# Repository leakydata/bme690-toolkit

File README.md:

# bme690-toolkit

Open tooling for Bosch's **BME690** and **BME688** gas sensors on Linux —
capture data, feed it to BME AI-Studio, and train models to recognise smells.

Bosch make excellent sensors and ship almost no usable software with them. The
shuttle boards arrive empty, AI-Studio is Windows-only and hard to even find,
and the file format that connects a capture to the training tool is
undocumented. This repository fills those gaps.

> Not affiliated with, endorsed by, or supported by Bosch Sensortec GmbH.

## What's here

| | |
|---|---|
| **[`bme690` CLI](python/)** | Reads all eight sensors on a BME690 8x shuttle over USB and writes AI-Studio-importable files |
| **[BME Studio](studio/)** | Browser app, an open alternative to BME AI-Studio: import, explore, label and train, with honest test scores and live predictions over USB. [Open it](https://leakydata.github.io/bme690-toolkit/studio/) |
| **[Python lab](python/LAB.md)** | `bme690.lab` for researchers with a GPU: pandas data loading, honest cross-validation, deep models across all sensors and over time, self-supervised pre-training, models back to BME Studio. Notebooks included |
| **[`.bmerawdata` format spec](docs/bmerawdata-format.md)** | The undocumented format AI-Studio imports, reverse-engineered and verified |
| **[Wiring guide](docs/wiring.md)** | Shuttle board and microSD to an ESP32-S3 DevKitC-1: diagram, pin tables with header positions, and the wiring check |
| **[Hardware notes](docs/hardware-notes.md)** | AB3.1 + shuttle pinout, flash layout, and the traps that cost days |
| **[AI-Studio on Linux](scripts/rebuild-aistudio-linux.sh)** | Turns Bosch's Windows release into a native Linux install |
| **[ESP32-S3 firmware](firmware/bme690-logger-idf/)** | Runs the shuttle from a cheap ESP32-S3 with no Application Board: records AI-Studio files to SD, WiFi dashboard, plain-English wiring diagnosis |

## Quick start

**No Application Board?** Wire the shuttle to an ESP32-S3 DevKitC and install
the firmware from your browser at
**[leakydata.github.io/bme690-toolkit](https://leakydata.github.io/bme690-toolkit/)**,
with nothing to install. That is the easiest way in, and what most people
should use. Details are in
[firmware/bme690-logger-idf](firmware/bme690-logger-idf/).

The rest of this section drives the shuttle on Bosch's Application Board 3.1
from a PC.

Hardware: a **BME690 8x shuttle board** on a **Bosch Application Board 3.1**,
running the stock `coines_bridge` firmware (how it ships), connected by USB.

```bash
git clone https://github.com/leakydata/bme690-toolkit
cd bme690-toolkit
python3 -m venv .venv && . .venv/bin/activate
pip install -e "python/[board]"

bme690 info      # board, firmware, all eight sensor IDs
bme690 read -n 5 # live readings from every sensor
```

You should see something like:

```
Board            : 0x9 (Application Board 3.1)
Shuttle          : 0x57
Firmware         : v1.8.6
Sensors detected : 8 -> [0, 1, 2, 3, 4, 5, 6, 7]
  sensor 0: chip 0x61  variant 2  uid 0xd737182e
  ...
```

Add yourself to the `dialout` group if the board is not reachable.

## Recording data for AI-Studio

```bash
# a labelled run: 5 min with the sample present, then 5 min of clean air
bme690 record -o coffee.bmerawdata --labels "coffee:300,air:300"
```

This writes `coffee.bmerawdata` and `coffee.bmelabelinfo`. In AI-Studio:
**Import Data → Specimen Raw Data**. The labelled segments arrive as named
specimens, ready to assign to classes and train on.

Defaults match Bosch's standard scanning setup: heater profile **HP-354**
(ten steps, 140 ms time base, 10.78 s per cycle), continuous duty cycle.

### Stabilise new sensors first

Factory-new sensors drift badly — gas resistance can move several-fold in
minutes. Bosch recommend at least 12 hours of stabilisation before any
training data is worth collecting:

```bash
bme690 burn-in --hours 12
```

Run it under `tmux`, somewhere with clean, still air.

## Commands

```
bme690 info                  board, firmware, sensor IDs
bme690 scan                  which sensor sockets answer
bme690 read -n 5 -i 2        forced-mode measurements
bme690 profiles              heater and duty cycle profiles AI-Studio knows
bme690 record -o F [...]     record a scan to .bmerawdata
bme690 burn-in --hours 12    stabilise the sensors
bme690 ingest -o F --port P  convert the ESP32-S3 logger's USB output to .bmerawdata
bme690 monitor [--port P]    live terminal view of the ESP32-S3 logger (curses)
```

### Two capture paths, one file format

| path | hardware | command |
|---|---|---|
| USB, host-driven | shuttle on an Application Board 3.1 | `bme690 record` |
| standalone firmware | shuttle on an ESP32-S3 | none: files are written to the SD card; or `bme690 ingest` over USB |

Both produce identical `.bmerawdata`, so captures from either import into the
same AI-Studio project.

```bash
# stream from the ESP32-S3 logger straight into a labelled capture
bme690 ingest --port /dev/ttyUSB0 -o coffee.bmerawdata --labels "coffee:300,air:300"

# or convert a log you captured earlier
cat /dev/ttyUSB0 > run.txt
bme690 ingest --from-file run.txt -o coffee.bmerawdata
```

`profiles` reads its catalogue from an AI-Studio installation, or from
`--config-dir` pointing at a directory holding `heater_profiles.json` and
`duty_cycle_profiles.json`.

## How it works

The Application Board 3.1 ships running Bosch's **COINES bridge firmware**,
which lets a host drive the shuttle board's SPI bus over USB. `bme690` talks
to it through the `coinespy` package, so **no reflashing is needed**.

- `device.py` — a Python port of Bosch's `bme69x.c` (float compensation path)
- `board.py` — the eight sensors and their SPI chip-selects
- `recorder.py` — parallel-mode scanning, where each sensor walks its ten-step
  heater profile autonomously and tags every result with the step index
- `rawdata.py` — the `.bmerawdata` / `.bmelabelinfo` writer

Two things that will bite you if you write your own: **coinespy takes volts,
not millivolts**, and **the SPI bus must be configured before the supply is
switched on**. Both are explained in [hardware notes](docs/hardware-notes.md);
`AppBoard31.open()` handles them.

## BME AI-Studio on Linux

AI-Studio is an Electron app, so its application code is portable JavaScript.
Only three native modules are Windows-specific — `better-sqlite3`, `sqlite3`
and `@tensorflow/tfjs-node`. Swap in Linux builds of the same versions, pair
with a Linux Electron 19.1.9 runtime, and it runs natively: project database,
TensorFlow training, BSEC export, all of it. No Wine.

```bash
scripts/rebuild-aistudio-linux.sh /path/to/bme_ai_studio_desktop_v3-1-0_win2
```

You supply Bosch's Windows release; the script contains no Bosch code.

## Which board is which

| board | interface | tooling |
|---|---|---|
| **BME690 8x shuttle** on an ESP32-S3 DevKitC | SD card, WiFi dashboard, USB | [firmware/bme690-logger-idf](firmware/bme690-logger-idf/) |
| **BME690 8x shuttle** on Application Board 3.1 | USB (COINES bridge) | `bme690`, this repo |
| **BME688 Development Kit** (8 sensors on ESP32) | SD card + BLE | AI-Studio board config + Bosch's mobile app |

The ESP32 dev kit runs its own autonomous firmware and is not driven by this
tool. Both produce `.bmerawdata`, so their data sits side by side in one
AI-Studio project — useful for cross-checking one sensor generation against
the other.

## Roadmap

The ESP32-S3 firmware does what the Application Board was meant to do:

- [x] Standalone scan, logging `.bmerawdata` to an SD card
- [x] Button and RGB LED: next sample label, start/stop
- [x] Retrieval by card reader or WiFi download
- [x] Heater profiles and duty cycles from AI-Studio `.bmeconfig` files
- [x] Wiring and sensor diagnosis in plain English
- [x] Built-in burn-in (Bosch HP-001)
- [x] Flash from the browser, so no toolchain is needed
- [ ] Battery operation
- [ ] BLE service and a phone app for field capture

`firmware/bme690-logger` is an earlier Zephyr build for a bare nRF52840. It is
no longer maintained and is kept for reference.

## Licensing

MIT, but it builds on Bosch software that is not. See
**[THIRD_PARTY.md](THIRD_PARTY.md)** — in short: the COINES SDK is fetched
rather than vendored, `coinespy` comes from PyPI, and BSEC and AI-Studio are
never distributed here.

```bash
scripts/setup-coines.sh   # needed only to build firmware
```

## Contributing

Issues and pull requests welcome — especially reports from other hardware
combinations. If you have a BME690 shuttle with a different EEPROM id, or an
AB3.1 with different firmware, please open an issue with `bme690 info` output.

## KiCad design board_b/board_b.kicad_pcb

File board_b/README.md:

# Board B: XIAO ESP32-S3 shuttle carrier

A 25.5 x 24.6 mm sandwich. A **Bosch Shuttle Board 3.0** plugs in on top
(made for the BME690 8x shuttle, and switchable to single-sensor shuttles).
A **Seeed XIAO ESP32-S3** or **XIAO ESP32-S3 Sense** plugs in underneath,
its USB-C at the P1 end.

**3.3 V only.** The XIAO's 3V3 pin powers the shuttle; it supplies up to
700 mA, and eight BME690 heaters need about 100 mA.

## Pin map

| XIAO | ESP32-S3 | shuttle | BME690 8x shuttle |
|---|---|---|---|
| D0 | GPIO1 | P1-4 (via JP2) | sensor U1 chip select |
| D1 | GPIO2 | P1-5 | U2 chip select |
| D2 | GPIO3 | P1-6 | U3 chip select |
| D3 | GPIO4 | P1-7 | U4 chip select |
| D4 | GPIO5 | P2-5 | U5 chip select |
| D5 | GPIO6 | P2-6 | U6 chip select |
| D6 | GPIO43 | P2-7 | U7 chip select |
| D7 | GPIO44 | P2-8 (via JP5) | U8 chip select |
| D8 | GPIO7 | P2-2 SCK/SCL | SPI clock |
| D9 | GPIO8 | P2-3 SDO | SPI data from the sensors (MISO) |
| D10 | GPIO9 | P2-4 SDI/SDA | SPI data to the sensors (MOSI) |
| 3V3 | | P1-2 VDDIO, and P1-1 VDD via JP1 | power |
| GND | | P1-3 | ground |
| 5V | | not connected | |

Two things about these pins:

- **D6 (GPIO43)** is the ESP32-S3's UART TX. The chip prints its boot
  messages there for a moment at power-up. That's harmless as a chip
  select, because nothing clocks the bus yet, but the firmware has to use
  the USB port for its console. The XIAO does this anyway.
- **D2 (GPIO3)** is a strapping pin, but only if the JTAG eFuse is burned;
  on a normal XIAO it's an ordinary GPIO.

### XIAO ESP32-S3 Sense

The Sense's microSD card uses **D8-D10 (the same SPI bus) plus GPIO21**
for its chip select. On this board the card and the sensors share one SPI
bus, each with its own chip select. On the Sense, GPIO21 is also the
orange user LED.

Seeed's design files suggest a catch, though. The Sense's camera/SD
expansion board is the XIAO's full width and covers the edge where header
pins are soldered. If so, a Sense with headers can't have its expansion
board fitted. Check yours: fit the expansion board and see whether the
pin holes along both long edges stay clear. Without the expansion board, a
Sense works here like a plain XIAO: live data over USB and WiFi, no card.

## Selector jumpers

**JP2 (D0) and JP5 (D7)** are 3-pad jumpers, made with **pads 1-2
joined** for the BME690 8x shuttle. The joined pair is the one with the
copper bridge.

| jumper | 1-2 (as made) | 2-3 |
|---|---|---|
| JP2 | D0 to shuttle GPIO0: U1 chip select (8x) | D0 to shuttle **CS**, for single-sensor shuttles |
| JP5 | D7 to shuttle GPIO7: U8 chip select (8x) | D7 to **PROM_RW**, the shuttle's ID chip |

**For a single-sensor shuttle**, cut the bridge on both and solder pads
2-3 together. With JP2 set this way, CS has a 10k pull-up, so the shuttle
starts in I2C mode; drive D0 low before the first transfer for SPI. Either
way its SCK/SDI/SDO are on D8/D10/D9, and its INT1/INT2 (P1-6, P1-7) are
on D2/D3.

### Other jumpers

All of these are closed as made:

| jumper | label | open it to |
|---|---|---|
| JP1 | IDD | measure sensor current: put a meter across J3 |
| JP3 | SDA | remove the 4.7k SDA pull-up |
| JP4 | SCL | remove the 4.7k SCL pull-up |

VDDIO is wired straight to the XIAO's 3V3, because it must match the XIAO's
logic level. So unlike Board A there is no TIE jumper.

PROM_RW has a 1k pull-up (the DS28E05 datasheet requires 300-1500 ohm). Its
1-Wire timing is overdrive only; see `board_a/README.md`.

## Assembly

JLCPCB fits the eight 0603 parts on top. You solder the rest:

1. **XIAO sockets first,** on the **bottom** (the side with the XIAO
   outline and "USB"). Plug both 1x7 sockets onto the XIAO's headers and
   set the XIAO in place. That holds them straight and 15.24 mm apart.
   Tack one pin of each, check they're square, then solder the rest from
   the top side.
2. **Trim their pins flush** on the top side. The shuttle sits above them.
3. **Shuttle sockets** on the **top**. Hold them in place with the shuttle,
   as described in board A's README.
4. **J3** (optional), on top.
5. Check with a meter: 3V3 to GND is **not** a short.

Solder the XIAO's own pin headers with the long pins coming out of its
underside, the side without the USB connector, as usual. The XIAO then
plugs in with its USB-C at the P1 end, and its buttons and antenna jack
facing away from the board.

## Firmware

The logger firmware has a build for this board (from version 2.4), with the
same dashboard, AI-Studio files and features as the DevKitC version:

| how | what to do |
|---|---|
| browser | at [leakydata.github.io/bme690-toolkit](https://leakydata.github.io/bme690-toolkit/), click **Install for XIAO ESP32-S3 (Board B)**. If the port doesn't appear, hold the XIAO's B button while plugging it in |
| WiFi update | `bme690-logger-xiao-app.bin`, from the same page |
| from source | `idf.py -B build-xiao -DBME690_BOARD=xiao build` in `firmware/bme690-logger-idf` |

What's different on the XIAO:

- **A plain XIAO ESP32-S3 works too**, live only: the dashboard's live
  graphs, **Record here** (recording into your browser), and USB streaming
  to BME Studio or the `bme690` tool. With no card, the dashboard shows a
  note (not a warning) and the LED blinks normally. Card recording needs
  the Sense with its camera/SD board fitted.
- The serial console is the XIAO's USB-C.
- The orange LED blinks the status: long = recording, short = not
  recording, double = warning or problem. It stays off while a Sense card
  is mounted, because on the Sense the LED pin is the card's chip select.
- The Sense's card shares the sensor bus. The firmware switches every
  sensor to SPI mode before the card is touched, and locks the bus for
  each transfer, so the two never talk over each other.

**Not yet tested on hardware.** Both builds compile cleanly. The first
power-up should be checked on the dashboard's Health tab.

## Ordering at JLCPCB

Everything is in `fab/`, in the same format as Board A:

| file | upload as |
|---|---|
| `board_b-gerbers.zip` | the PCB |
| `board_b-bom-jlcpcb.csv` | PCB Assembly: BOM |
| `board_b-cpl-jlcpcb.csv` | PCB Assembly: CPL |

The options, coupon notes and pre-order checklist are the same as in
`board_a/README.md`, with these differences:

| check | Board B |
|---|---|
| board size | 25.5 x 24.6 mm |
| holes | 42 (10 vias, 16 shuttle socket holes, 16 header holes) |
| assembly | Economic, top side |
| SMD parts | the same eight Basic parts as Board A |

### Parts JLCPCB fits

| parts | value | LCSC |
|---|---|---|
| R1, R2 | 4.7k 0603 | C23162 |
| R3 | 1k 0603 | C21190 |
| R4 | 10k 0603 | C25804 |
| C1, C3 | 100 nF 0603 | C14663 |
| C2, C4 | 10 uF 0603 | C19702 |

All are Basic; stock was checked 2026-10-05.

### Parts you buy

Per board:

| part | qty | about |
|---|---|---|
| Sullins LPPB071NFFN-RC, 7-pin 1.27 mm socket | 1 | $1.00 |
| Sullins LPPB091NFFN-RC, 9-pin 1.27 mm socket | 1 | $1.20 |
| Sullins PPTC071LFBN-RC, 1x7 female 2.54 mm, 8.5 mm tall | 2 | $0.70 each |
| 1x2 male header, 2.54 mm (optional, for IDD) | 1 | $0.05 |
| Seeed XIAO ESP32-S3 (or the Sense) | 1 | see seeedstudio.com |

## Cost estimate, 5 boards

The same as Board A, since it uses the same eight parts on a board under
100 x 100 mm:

| order | before shipping | with shipping and duty |
|---|---|---|
| bare PCBs | about $3-4 | about $7-10 by the cheapest shipping |
| PCB + Economic assembly | about $13-15 | about $17-22 |

**Ordering A and B together:** two designs are two PCB line items. The
assembly setup and stencil fees ($8.18 + $1.53) are charged per design,
but you pay shipping once.

## Design rules

The same JLCPCB rules as Board A. Results: ERC 0, DRC 0 (warnings
included), schematic parity 0.

The XIAO footprint's courtyard covers its two sockets only. The module
itself rides 8.5 mm up on them, well above the shuttle socket's 3 mm pin
tails that pass beneath it. DRC therefore doesn't flag those tails.

## Editing

Open `board_b.kicad_pro` in KiCad 10. `build.py` and `pcb.py` generated
the first version. Edit in KiCad from here on; re-running the scripts
overwrites your changes.

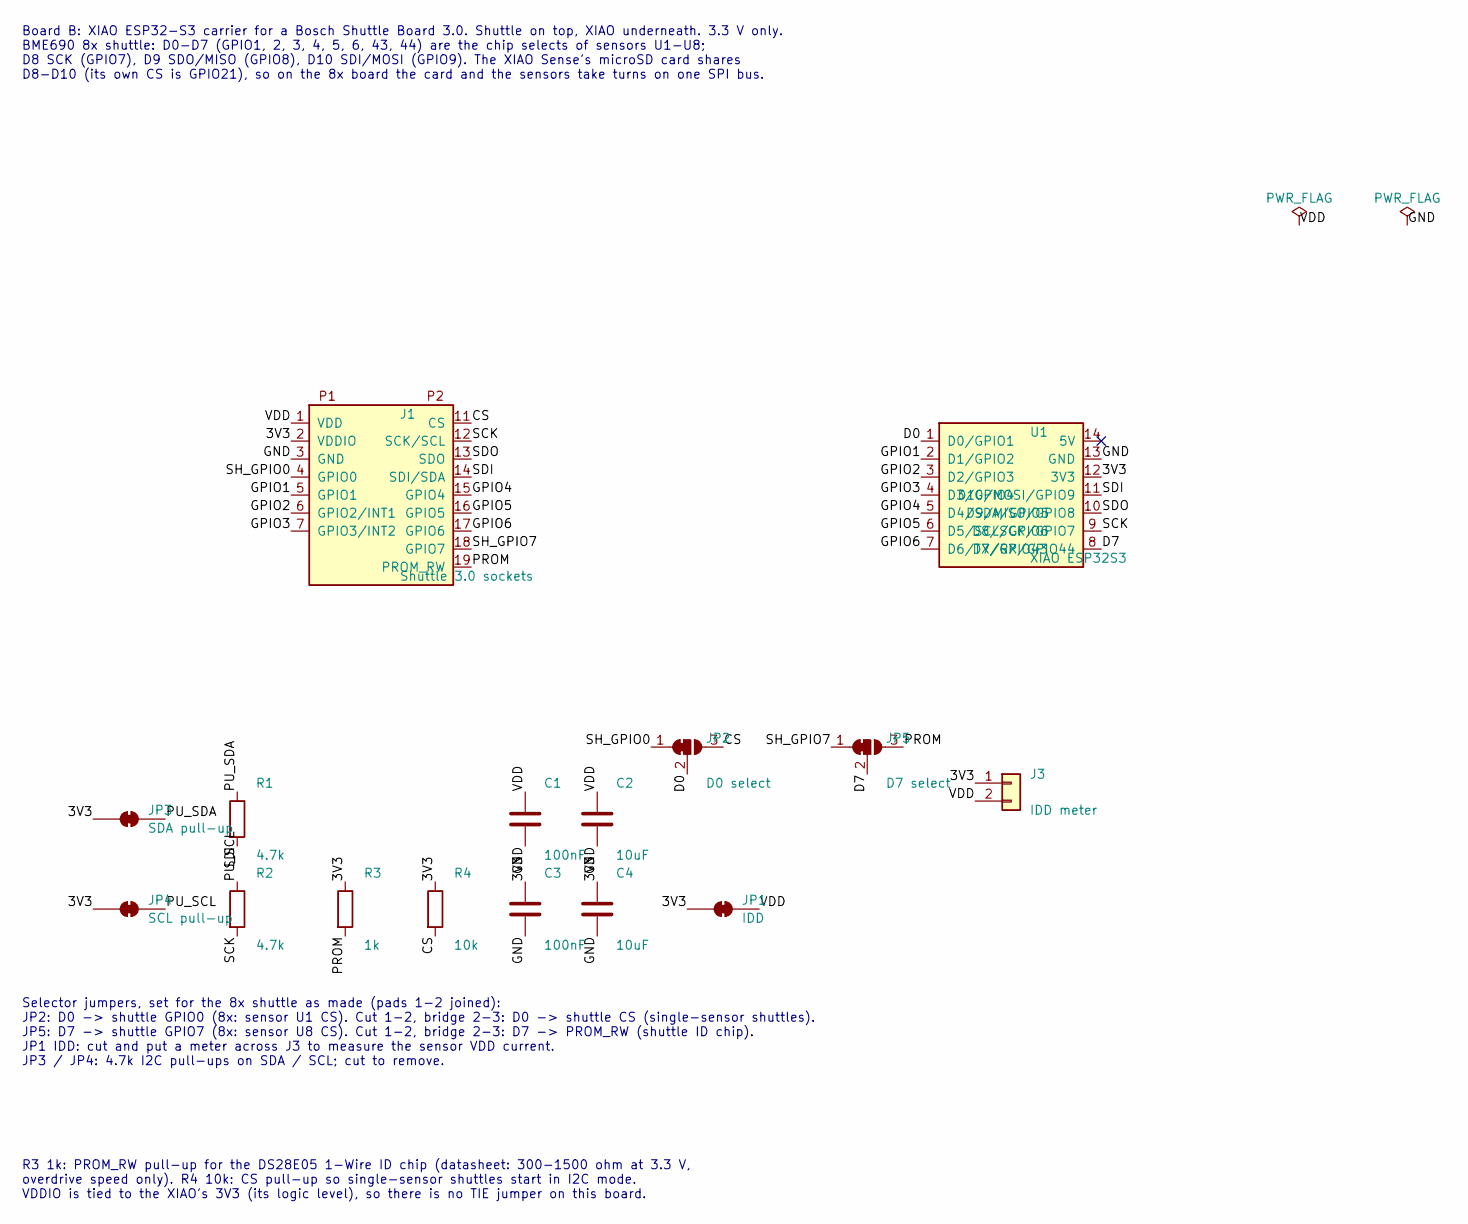
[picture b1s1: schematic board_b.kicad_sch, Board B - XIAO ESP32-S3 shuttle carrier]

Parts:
C1, C3: 100nF; C_0603_1608Metric; LCSC C14663
C2, C4: 10uF; C_0603_1608Metric; LCSC C19702
J1: Shuttle 3.0 sockets; Bosch_Shuttle_3.0_Sockets; MPN Sullins LPPB071NFFN-RC + LPPB091NFFN-RC
J3: IDD meter; PinHeader_1x02_P2.54mm_Vertical; MPN 1x2 male header 2.54 mm
JP1: IDD; SolderJumper-2_P1.3mm_Bridged_RoundedPad1.0x1.5mm
JP2: D0 select; SolderJumper-3_P1.3mm_Bridged12_RoundedPad1.0x1.5mm
JP3: SDA pull-up; SolderJumper-2_P1.3mm_Bridged_RoundedPad1.0x1.5mm
JP4: SCL pull-up; SolderJumper-2_P1.3mm_Bridged_RoundedPad1.0x1.5mm
JP5: D7 select; SolderJumper-3_P1.3mm_Bridged12_RoundedPad1.0x1.5mm
R1, R2: 4.7k; R_0603_1608Metric; LCSC C23162
R3: 1k; R_0603_1608Metric; LCSC C21190
R4: 10k; R_0603_1608Metric; LCSC C25804
U1: XIAO ESP32S3; XIAO_ESP32S3_THT; MPN 2x Sullins PPTC071LFBN-RC (1x7 female 2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

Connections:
/3V3: C3.1, C4.1, J1.2 (VDDIO), J3.1, JP1.1 (A), JP3.1 (A), JP4.1 (A), R3.1, R4.1, U1.12 (3V3)
/CS: J1.11 (CS), JP2.3 (B), R4.2
/D0: JP2.2 (C), U1.1 (D0/GPIO1)
/D7: JP5.2 (C), U1.8 (D7/RX/GPIO44)
/GND: C1.2, C2.2, C3.2, C4.2, J1.3 (GND), U1.13 (GND)
/GPIO1: J1.5 (GPIO1), U1.2 (D1/GPIO2)
/GPIO2: J1.6 (GPIO2/INT1), U1.3 (D2/GPIO3)
/GPIO3: J1.7 (GPIO3/INT2), U1.4 (D3/GPIO4)
/GPIO4: J1.15 (GPIO4), U1.5 (D4/SDA/GPIO5)
/GPIO5: J1.16 (GPIO5), U1.6 (D5/SCL/GPIO6)
/GPIO6: J1.17 (GPIO6), U1.7 (D6/TX/GPIO43)
/PROM: J1.19 (PROM_RW), JP5.3 (B), R3.2
/PU_SCL: JP4.2 (B), R2.1
/PU_SDA: JP3.2 (B), R1.1
/SCK: J1.12 (SCK/SCL), R2.2, U1.9 (D8/SCK/GPIO7)
/SDI: J1.14 (SDI/SDA), R1.2, U1.11 (D10/MOSI/GPIO9)
/SDO: J1.13 (SDO), U1.10 (D9/MISO/GPIO8)
/SH_GPIO0: J1.4 (GPIO0), JP2.1 (A)
/SH_GPIO7: J1.18 (GPIO7), JP5.1 (A)
/VDD: C1.1, C2.1, J1.1 (VDD), J3.2, JP1.2 (B)

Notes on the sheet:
Board B: XIAO ESP32-S3 carrier for a Bosch Shuttle Board 3.0. Shuttle on top, XIAO underneath. 3.3 V only. BME690 8x shuttle: D0-D7 (GPIO1, 2, 3, 4, 5, 6, 43, 44) are the chip selects of sensors U1-U8; D8 SCK (GPIO7), D9 SDO/MISO (GPIO8), D10 SDI/MOSI (GPIO9). The XIAO Sense's microSD card shares D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
Selector jumpers, set for the 8x shuttle as made (pads 1-2 joined): JP2: D0 -> shuttle GPIO0 (8x: sensor U1 CS). Cut 1-2, bridge 2-3: D0 -> shuttle CS (single-sensor shuttles). JP5: D7 -> shuttle GPIO7 (8x: sensor U8 CS). Cut 1-2, bridge 2-3: D7 -> PROM_RW (shuttle ID chip). JP1 IDD: cut and put a 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
R3 1k: PROM_RW pull-up for the DS28E05 1-Wire ID chip (datasheet: 300-1500 ohm at 3.3 V, overdrive speed only). R4 10k: CS pull-up so single-sensor shuttles start in I2C mode. VDDIO is tied to the XIAO's 3V3 (its logic level), so there is no TIE jumper on this board.

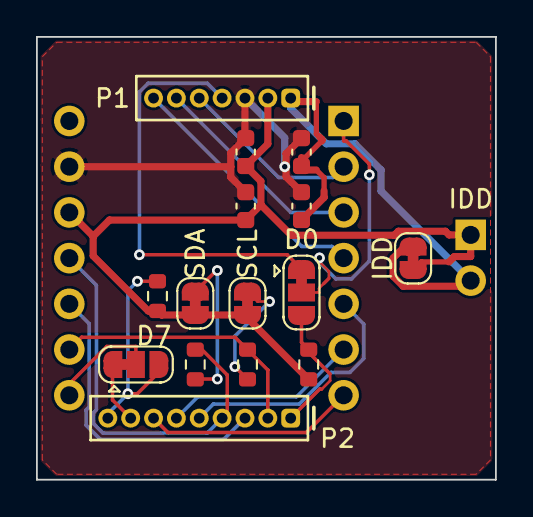
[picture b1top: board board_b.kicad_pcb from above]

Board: 2 copper layers, 25.5 x 24.6 mm, 16 parts (1 on the bottom side), 20 nets.

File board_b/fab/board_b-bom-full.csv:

Designator,Value,Footprint,LCSC,MPN,Fitted by
C1,100nF,C_0603_1608Metric,C14663,,JLCPCB
C2,10uF,C_0603_1608Metric,C19702,,JLCPCB
C3,100nF,C_0603_1608Metric,C14663,,JLCPCB
C4,10uF,C_0603_1608Metric,C19702,,JLCPCB
J1,Shuttle 3.0 sockets,Bosch_Shuttle_3.0_Sockets,,Sullins LPPB071NFFN-RC + LPPB091NFFN-RC,you (hand solder)
J3,IDD meter,PinHeader_1x02_P2.54mm_Vertical,,1x2 male header 2.54 mm,you (hand solder)
R1,4.7k,R_0603_1608Metric,C23162,,JLCPCB
R2,4.7k,R_0603_1608Metric,C23162,,JLCPCB
R3,1k,R_0603_1608Metric,C21190,,JLCPCB
R4,10k,R_0603_1608Metric,C25804,,JLCPCB
U1,XIAO ESP32S3,XIAO_ESP32S3_THT,,"2x Sullins PPTC071LFBN-RC (1x7 female 2.54 mm, 8.5 mm) for a Seeed XIAO ESP32S3 / Sense",you (hand solder)

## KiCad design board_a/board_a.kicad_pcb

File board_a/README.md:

# Board A: Shuttle 3.0 breakout

A 29.3 x 26.2 mm board that takes **any Bosch Sensortec Shuttle Board 3.0**,
including the BME690 8x shuttle, and brings all 16 of its pins out to a
labelled 2.54 mm header for Dupont wires, a breadboard ribbon or a
microcontroller.

## What's on it

| part | job |
|---|---|
| J1 | shuttle sockets: P1 (7 pins) and P2 (9 pins), 1.27 mm. A 7-pin and a 9-pin socket, so the shuttle only fits one way |
| J2 | 2x8 2.54 mm header with every shuttle pin |
| J3 | 2 pins for measuring the sensor's VDD current (IDD) |
| R1, R2 | 4.7k I2C pull-ups on SDA and SCL, each behind a cut jumper |
| R3 | 1k pull-up on PROM_RW, the shuttle's ID chip |
| R4 | 10k pull-up on CS, so single-sensor shuttles start in I2C mode |
| C1-C4 | 100 nF + 10 uF on VDD, and the same on VDDIO |

**3.3 V only. Never connect 5 V.**

## Header pin map (J2)

The column next to the shuttle carries its GPIO0-7, and the outer column
carries power and the bus. Both sides of the board are labelled, and a dot
marks pin 1.

| row | inner pin | inner label | signal | outer pin | outer label | signal |
|---|---|---|---|---|---|---|
| 1 | 1 | 0 | GPIO0 (P1-4) | 2 | VIO | VDDIO (P1-2) |
| 2 | 3 | 1 | GPIO1 (P1-5) | 4 | VDD | VDD supply in |
| 3 | 5 | 2 | GPIO2/INT1 (P1-6) | 6 | GND | GND (P1-3) |
| 4 | 7 | 3 | GPIO3/INT2 (P1-7) | 8 | SCK | SCK/SCL (P2-2) |
| 5 | 9 | 4 | GPIO4 (P2-5) | 10 | SDO | SDO (P2-3) |
| 6 | 11 | 5 | GPIO5 (P2-6) | 12 | SDI | SDI/SDA (P2-4) |
| 7 | 13 | 6 | GPIO6 (P2-7) | 14 | CS | CS (P2-1) |
| 8 | 15 | 7 | GPIO7 (P2-8) | 16 | ID | PROM_RW (P2-9) |

On the **BME690 8x shuttle**, GPIO0-7 are the chip selects of sensors
U1-U8, and CS (P2-1) isn't connected to anything. The 8x shuttle only works
over SPI: in I2C mode all eight sensors would answer at the same address.

## Solder jumpers

All four are **closed as made**. To open one, cut the thin trace between
its pads with a sharp knife. To close it again, bridge the pads with solder.

| jumper | label | open it to |
|---|---|---|
| JP1 | IDD (bottom left of J3) | measure sensor current: put a meter across J3 |
| JP2 | TIE | power VDDIO separately from VDD (feed VIO yourself) |
| JP3 | SDA | remove the 4.7k SDA pull-up |
| JP4 | SCL | remove the 4.7k SCL pull-up |

With TIE closed, one 3.3 V wire to **VIO** or **VDD** powers everything.

## Which side for the header?

The header is hand-soldered, so you choose:

- **Pins down, on the back:** best for sniffing jars. The sensors face the
  sample and the wires leave from the other side, so the plastic and wire
  insulation stay out of the air being measured.
- **Pins up, on the front:** easiest on a bench.
- **Right-angle header:** the wires leave sideways and the board lies flat.
  Its body covers the labels on that side, but the other side is labelled
  too.

**To a breadboard:** use a 16-way ribbon cable with a 2x8 IDC socket on
one end and a 16-pin DIP IDC plug on the other. Put the red stripe at the
pin-1 dot. The plug sits across the breadboard's centre gap. Its pins
alternate between the two DIP rows, so check the plug's datasheet for which
conductor lands where. A flat ribbon also passes a jar lid's seal far
better than loose jumpers.

## Assembly

JLCPCB fits the eight 0603 parts. You solder the through-hole parts.

1. Check the board under a light: all eight SMD parts present, no bridges.
2. **Sockets first.** Plug both sockets onto the shuttle and push the
   shuttle into the board. The shuttle holds the sockets straight and at
   the right spacing. Solder one end pin of each row, check they sit flat,
   then solder the rest. Remove the shuttle before it gets hot for long.
3. **2x8 header** on the side you chose. Solder one pin, check it's square,
   then the rest.
4. **J3** (optional), the same way.
5. Check with a meter: 3V3 to GND must **not** be a short. VIO to VDD
   reads about 0 ohm (TIE closed).

## Smoke test (ESP32-S3)

`smoke_test/smoke_test.ino` (Arduino IDE or arduino-cli, ESP32 core 3.x,
board "ESP32S3 Dev Module"). The wiring matches the logger firmware's pin
map, so a board wired for the logger runs the test unchanged.

| Board A | ESP32-S3 |
|---|---|
| VIO | 3V3 |
| GND | GND |
| SCK | GPIO12 |
| SDI | GPIO11 |
| SDO | GPIO13 |
| 0-7 | GPIO1, 2, 4, 5, 6, 7, 15, 16 |

- `MODE_SPI 1` (the default), for the 8x shuttle: reads the chip ID
  register of all eight sensors and expects **0x61** from each. A sensor
  that answers wrong names its chip-select wire.
- `MODE_SPI 0`, for a single-sensor shuttle: scans I2C and reads register
  0xD0 at **0x76**. It drives SDO low to set that address, because SDO
  must not float. Expect 0x61. Leave CS open; the 10k pull-up selects I2C.

For the full logger, see `firmware/bme690-logger-idf`.

**PROM_RW (shuttle ID):** the DS28E05 talks at 1-Wire **overdrive speed
only** (up to 76.9 kbps). The datasheet's overdrive timings are:

| timing | value |
|---|---|
| reset low | 48-80 us |
| presence sample | 8-10 us |
| write-0 low | 8-16 us |
| write-1 / read low | 1-2 us |
| sample by | 2 us |
| slot | 13 us minimum |
| EEPROM write | 16 ms per write |

Common ESP32 1-Wire libraries run at standard speed and won't see it. A
reader needs these timings, using the RMT peripheral or interrupt-free bit
timing. It isn't in the smoke test yet.

## Ordering at JLCPCB

All files are in `fab/`:

| file | upload as |
|---|---|
| `board_a-gerbers.zip` | the PCB (Gerbers + Excellon drill) |
| `board_a-bom-jlcpcb.csv` | PCB Assembly: BOM |
| `board_a-cpl-jlcpcb.csv` | PCB Assembly: CPL / pick-and-place |
| `board_a-bom-full.csv` | your shopping list, including the hand-soldered parts |
| `board_a-schematic.pdf`, `board_a-layout.pdf` | for checking |

**Board options:**

| option | setting |
|---|---|
| layers | 2 |
| thickness | 1.6 mm |
| material | FR-4 |
| solder mask | green |
| surface finish | **LeadFree HASL** |
| Mark on PCB | **Remove Mark** (free, and the default) |
| quantity | 5 |

**Assembly options:**

| option | setting |
|---|---|
| type | Economic |
| side | Top |
| boards to assemble | 5 (or 2, the minimum) |

### Parts JLCPCB fits

All are LCSC **Basic** parts, so there is no extended-part fee. Stock was
checked 2026-10-05.

| parts | value | LCSC | stock |
|---|---|---|---|
| R1, R2 | 4.7k 1% 0603 | C23162 | 22.2 M |
| R3 | 1k 1% 0603 | C21190 | 21.3 M |
| R4 | 10k 1% 0603 | C25804 | 29.6 M |
| C1, C3 | 100 nF X7R 50 V 0603 | C14663 | 57.2 M |
| C2, C4 | 10 uF X5R 10 V 0603 | C19702 | 10.3 M |

### Parts you buy and solder

Per board:

| part | qty | about |
|---|---|---|
| Sullins LPPB071NFFN-RC, 7-pin 1.27 mm socket | 1 | $1.00 |
| Sullins LPPB091NFFN-RC, 9-pin 1.27 mm socket | 1 | $1.20 |
| 2x8 male header, 2.54 mm (straight or right angle) | 1 | $0.30 |
| 1x2 male header, 2.54 mm (optional, for IDD) | 1 | $0.05 |

## Cost estimate, 5 boards

These are estimates from JLCPCB's published prices (October 2026). The quote
page gives the real figure.

| | bare PCB | PCB + assembly |
|---|---|---|
| 5 PCBs, 2-layer, under 100 x 100 mm | $2 | $2 |
| lead-free HASL surcharge | about $1-1.50 | about $1-1.50 |
| assembly setup (Economic) | - | $8.18 |
| stencil | - | $1.53 |
| solder joints, 80 x $0.0016 | - | $0.13 |
| parts: 5 Basic lines, LCSC minimum quantities | - | about $0.50-1 |
| extended-part fees | - | $0 (none) |
| **subtotal before shipping** | **about $3-4** | **about $13-15** |
| US shipping, Global Standard Direct (slowest, cheapest) | about $1.50-4 | about $2-5 |
| US shipping, DHL / UPS / FedEx express | about $15-25 | about $15-25 |
| US import duty (DDP, pre-collected) | a few dollars | a few dollars |

Plus about $13 for the hand-soldered parts for 5 boards, with distributor
shipping on top.

**Duties.** JLCPCB ships to US individuals **DDP (Delivered Duty Paid)**:
the import duty is calculated and charged at checkout, so nothing is due on
delivery. It is mandatory for individual customers. Business accounts may
choose CPT and pay duty themselves. JLCPCB revised its US rates on
2026-03-17, after the February 2026 tariff change. The exact amount appears
on the checkout page.

**Coupons.**
- **When it applies:** the coupon is chosen on the **checkout / payment
  page**, after you enter the shipping address. Available coupons are
  listed there, and a code (such as a YouTube sponsor code) goes in the
  coupon box on the right of the order summary.
- **One per order:** only one coupon can be used per order, and coupons
  can't be combined. Pick the larger of your sponsor code and the
  new-customer coupon.
- **New-customer coupons:** $6 off PCB orders over $2, or $10 off SMT
  assembly orders over $2, with **shipping not counted** toward the
  minimum. A separate $10 shipping coupon needs $15 of shipping.

### Pre-order checklist

1. Upload `board_a-gerbers.zip`. The viewer should show 29.3 x 26.2 mm,
   2 layers and 39 holes, with the labels readable on both sides.
2. Set LeadFree HASL, green, 1.6 mm, and leave "Mark on PCB" at
   **Remove Mark**.
3. Turn on PCB Assembly: Economic, Top side, then upload the BOM and CPL.
4. On the parts page, check that all 8 parts matched (5 lines, all
   "Basic") and nothing is marked "shortage".
5. On the placement preview, check each part sits on its pads. R and C
   rotation doesn't matter (they aren't polarised), but each must sit
   squarely on both pads.
6. Choose shipping and check the DDP duty line.
7. Apply your coupon on the checkout page and check the total before
   paying.
8. Order the sockets and headers from a distributor (Digi-Key, Mouser,
   LCSC) at the same time.

## Design rules used

JLCPCB 2-layer capabilities (jlcpcb.com/capabilities, checked 2026-10-03),
with these values used:

| rule | used | JLCPCB minimum |
|---|---|---|
| clearance | 0.15 mm | 0.10 mm |
| minimum track | 0.15 mm (0.2 signal, 0.4 power) | 0.10 mm |
| vias | 0.6 mm pad, 0.3 mm hole | 0.25 / 0.15 mm |
| PTH annular ring | at least 0.225 mm (sockets) | 0.18 mm (0.25 recommended) |
| copper to board edge | 0.3 mm | 0.2 mm |
| hole to hole | 0.5 mm | 0.45 mm |
| silkscreen text | 1.0 mm high, 0.15 mm line | 1.0 / 0.15 mm |

ERC: 0 errors, 0 warnings. DRC, including warnings and schematic parity: 0.

## Editing

Open `board_a.kicad_pro` in KiCad 10. `build.py` and `pcb.py` generated
the first version: one parts list feeds both the schematic and the board,
with Freerouting for the tracks. Once you edit in KiCad, keep editing there.
Re-running the scripts overwrites your changes. The shared symbols and
footprints are in `../shuttle_lib`.

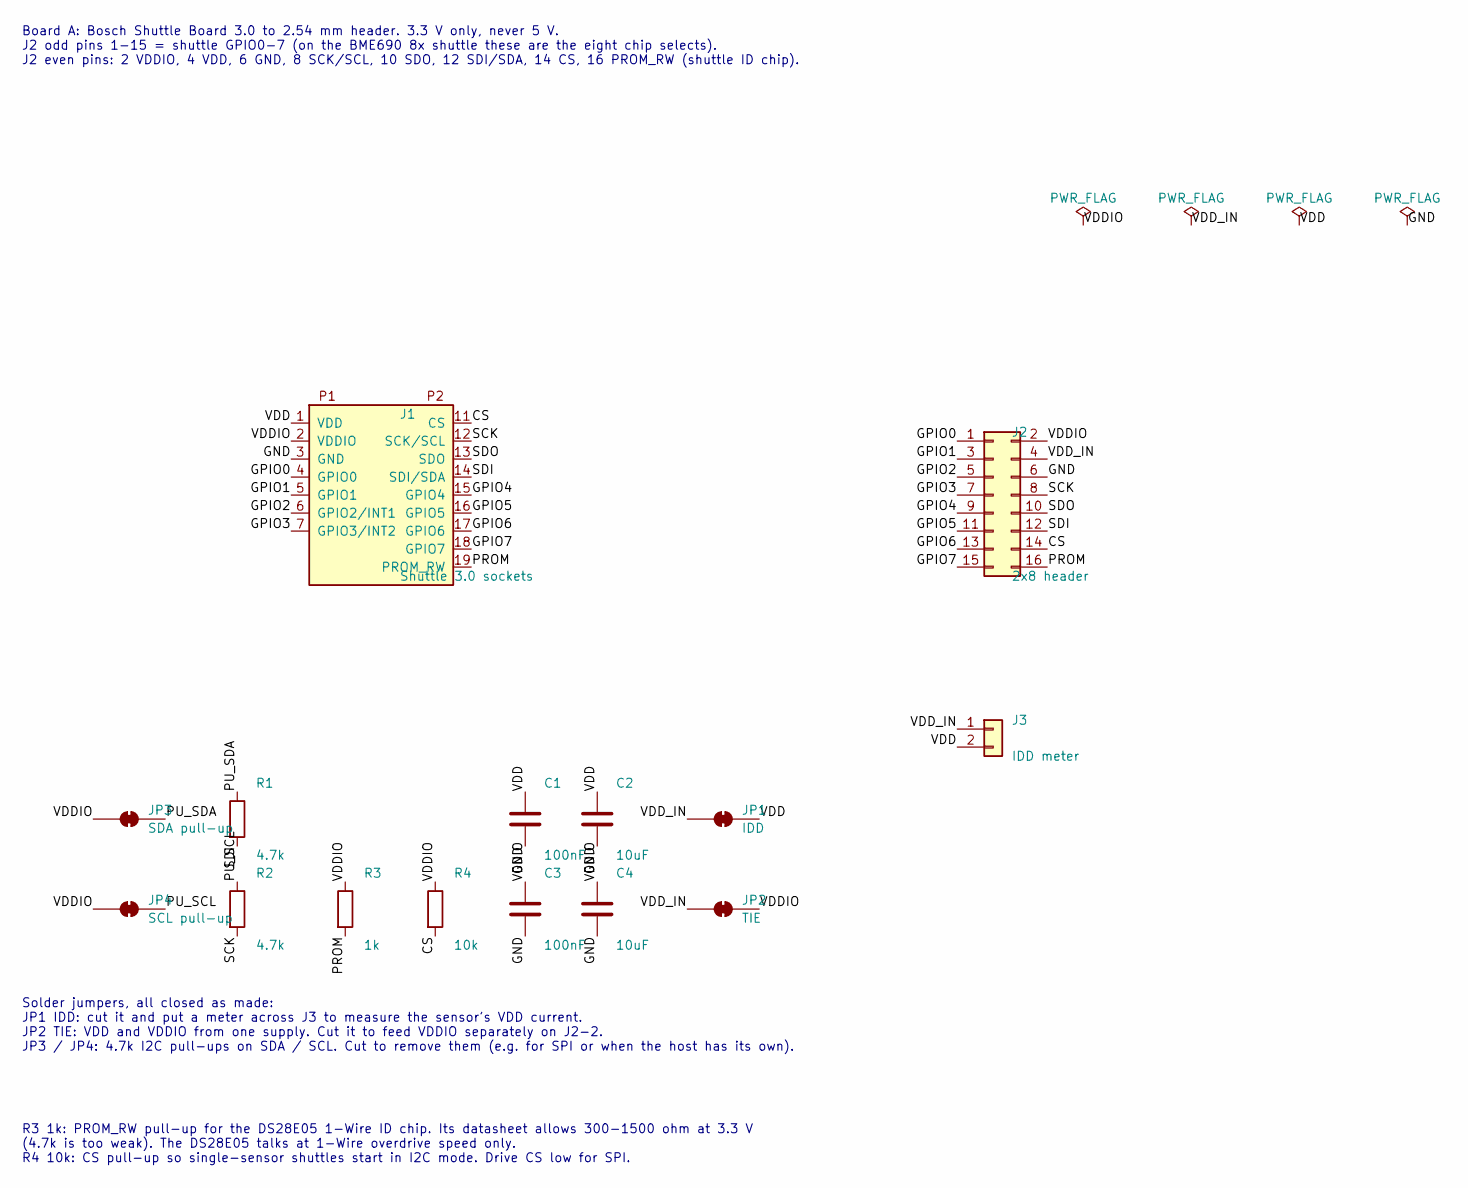
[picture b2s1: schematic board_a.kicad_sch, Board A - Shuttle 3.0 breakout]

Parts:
C1, C3: 100nF; C_0603_1608Metric; LCSC C14663
C2, C4: 10uF; C_0603_1608Metric; LCSC C19702
J1: Shuttle 3.0 sockets; Bosch_Shuttle_3.0_Sockets; MPN Sullins LPPB071NFFN-RC + LPPB091NFFN-RC
J2: 2x8 header; PinHeader_2x08_P2.54mm_Vertical; MPN 2x8 male header 2.54 mm
J3: IDD meter; PinHeader_1x02_P2.54mm_Vertical; MPN 1x2 male header 2.54 mm
JP1: IDD; SolderJumper-2_P1.3mm_Bridged_RoundedPad1.0x1.5mm
JP2: TIE; SolderJumper-2_P1.3mm_Bridged_RoundedPad1.0x1.5mm
JP3: SDA pull-up; SolderJumper-2_P1.3mm_Bridged_RoundedPad1.0x1.5mm
JP4: SCL pull-up; SolderJumper-2_P1.3mm_Bridged_RoundedPad1.0x1.5mm
R1, R2: 4.7k; R_0603_1608Metric; LCSC C23162
R3: 1k; R_0603_1608Metric; LCSC C21190
R4: 10k; R_0603_1608Metric; LCSC C25804

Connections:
/CS: J1.11 (CS), J2.14, R4.2
/GND: C1.2, C2.2, C3.2, C4.2, J1.3 (GND), J2.6
/GPIO0: J1.4 (GPIO0), J2.1
/GPIO1: J1.5 (GPIO1), J2.3
/GPIO2: J1.6 (GPIO2/INT1), J2.5
/GPIO3: J1.7 (GPIO3/INT2), J2.7
/GPIO4: J1.15 (GPIO4), J2.9
/GPIO5: J1.16 (GPIO5), J2.11
/GPIO6: J1.17 (GPIO6), J2.13
/GPIO7: J1.18 (GPIO7), J2.15
/PROM: J1.19 (PROM_RW), J2.16, R3.2
/PU_SCL: JP4.2 (B), R2.1
/PU_SDA: JP3.2 (B), R1.1
/SCK: J1.12 (SCK/SCL), J2.8, R2.2
/SDI: J1.14 (SDI/SDA), J2.12, R1.2
/SDO: J1.13 (SDO), J2.10
/VDD: C1.1, C2.1, J1.1 (VDD), J3.2, JP1.2 (B)
/VDDIO: C3.1, C4.1, J1.2 (VDDIO), J2.2, JP2.2 (B), JP3.1 (A), JP4.1 (A), R3.1, R4.1
/VDD_IN: J2.4, J3.1, JP1.1 (A), JP2.1 (A)

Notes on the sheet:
Board A: Bosch Shuttle Board 3.0 to 2.54 mm header. 3.3 V only, never 5 V. J2 odd pins 1-15 = shuttle GPIO0-7 (on the BME690 8x shuttle these are the eight chip selects). J2 even pins: 2 VDDIO, 4 VDD, 6 GND, 8 SCK/SCL, 10 SDO, 12 SDI/SDA, 14 CS, 16 PROM_RW (shuttle ID chip).
Solder jumpers, all closed as made: JP1 IDD: cut it and put a meter across J3 to measure the sensor's VDD current. JP2 TIE: VDD and VDDIO from one supply. Cut it to feed VDDIO separately on J2-2. JP3 / JP4: 4.7k I2C pull-ups on SDA / SCL. Cut to remove them (e.g. for SPI or when the host has its ow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
R3 1k: PROM_RW pull-up for the DS28E05 1-Wire ID chip. Its datasheet allows 300-1500 ohm at 3.3 V (4.7k is too weak). The DS28E05 talks at 1-Wire overdrive speed only. R4 10k: CS pull-up so single-sensor shuttles start in I2C mode. Drive CS low for SPI.

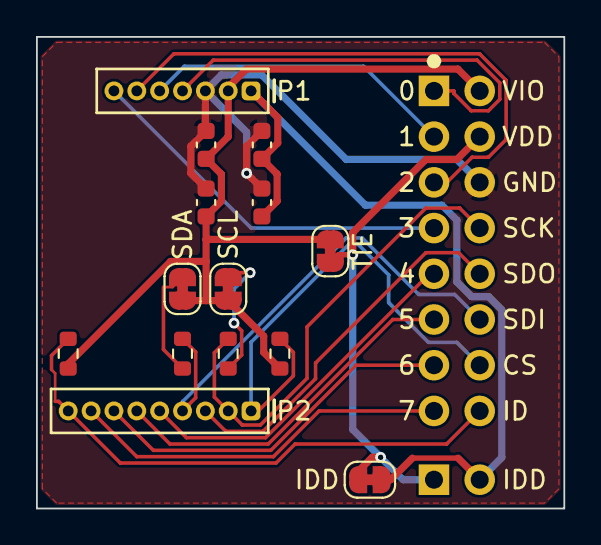
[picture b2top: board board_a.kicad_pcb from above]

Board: 2 copper layers, 29.3 x 26.2 mm, 15 parts (0 on the bottom side), 19 nets.

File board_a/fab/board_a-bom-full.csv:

Designator,Value,Footprint,LCSC,MPN,Fitted by
C1,100nF,C_0603_1608Metric,C14663,,JLCPCB
C2,10uF,C_0603_1608Metric,C19702,,JLCPCB
C3,100nF,C_0603_1608Metric,C14663,,JLCPCB
C4,10uF,C_0603_1608Metric,C19702,,JLCPCB
J1,Shuttle 3.0 sockets,Bosch_Shuttle_3.0_Sockets,,Sullins LPPB071NFFN-RC + LPPB091NFFN-RC,you (hand solder)
J2,2x8 header,PinHeader_2x08_P2.54mm_Vertical,,2x8 male header 2.54 mm,you (hand solder)
J3,IDD meter,PinHeader_1x02_P2.54mm_Vertical,,1x2 male header 2.54 mm,you (hand solder)
R1,4.7k,R_0603_1608Metric,C23162,,JLCPCB
R2,4.7k,R_0603_1608Metric,C23162,,JLCPCB
R3,1k,R_0603_1608Metric,C21190,,JLCPCB
R4,10k,R_0603_1608Metric,C25804,,JLCPCB

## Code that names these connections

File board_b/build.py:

"""Board B: Seeed XIAO ESP32-S3 (or ESP32-S3 Sense) carrier for a Bosch
Shuttle Board 3.0. The shuttle plugs in on top; the XIAO plugs into two
1x7 female sockets underneath.

Builds board_b.kicad_sch and board_b.kicad_pcb from the parts list below.
This script made the first version of the design; once you edit the files
in KiCad, edit them there rather than re-running it.

    python board_b/build.py sch      schematic + ERC
    python board_b/build.py pcb      placement, autoroute, zones + DRC
"""

import sys
from pathlib import Path

HERE = Path(__file__).resolve().parent
sys.path.insert(0, str(HERE.parent / "shuttle_lib" / "tools"))

from kigen import Part, write_lib_tables, write_project, write_schematic, netclass  # noqa: E402

NAME = "board_b"

R0603 = "Resistor_SMD:R_0603_1608Metric"
C0603 = "Capacitor_SMD:C_0603_1608Metric"
SJ2 = "Jumper:SolderJumper-2_P1.3mm_Bridged_RoundedPad1.0x1.5mm"
SJ3 = "Jumper:SolderJumper-3_P1.3mm_Bridged12_RoundedPad1.0x1.5mm"


def parts():
    return [
        Part("J1", "Shuttle3:Bosch_Shuttle_3.0", "Shuttle 3.0 sockets", "Shuttle3:Bosch_Shuttle_3.0_Sockets",
             {"1": "VDD", "2": "3V3", "3": "GND", "4": "SH_GPIO0", "5": "GPIO1", "6": "GPIO2", "7": "GPIO3",
              "11": "CS", "12": "SCK", "13": "SDO", "14": "SDI", "15": "GPIO4", "16": "GPIO5",
              "17": "GPIO6", "18": "SH_GPIO7", "19": "PROM"},
             mpn="Sullins LPPB071NFFN-RC + LPPB091NFFN-RC", at=(76.2, 88.9)),
        # D0-D7 are the 8x shuttle's chip selects, D8-D10 the SPI bus
        Part("U1", "Shuttle3:XIAO_ESP32S3", "XIAO ESP32S3", "Shuttle3:XIAO_ESP32S3_THT",
             {"1": "D0", "2": "GPIO1", "3": "GPIO2", "4": "GPIO3", "5": "GPIO4", "6": "GPIO5", "7": "GPIO6",
              "8": "D7", "9": "SCK", "10": "SDO", "11": "SDI", "12": "3V3", "13": "GND", "14": None},
             mpn="2x Sullins PPTC071LFBN-RC (1x7 female 2.54 mm, 8.5 mm) for a Seeed XIAO ESP32S3 / Sense",
             at=(165.1, 88.9)),
        Part("JP2", "Jumper:SolderJumper_3_Bridged12", "D0 select", SJ3,
             {"1": "SH_GPIO0", "2": "D0", "3": "CS"}, at=(119.38, 124.46), in_bom=False),
        Part("JP5", "Jumper:SolderJumper_3_Bridged12", "D7 select", SJ3,
             {"1": "SH_GPIO7", "2": "D7", "3": "PROM"}, at=(144.78, 124.46), in_bom=False),
        Part("J3", "Connector_Generic:Conn_01x02", "IDD meter", "Connector_PinHeader_2.54mm:PinHeader_1x02_P2.54mm_Vertical",
             {"1": "3V3", "2": "VDD"}, mpn="1x2 male header 2.54 mm", at=(165.1, 129.54)),
        Part("JP1", "Jumper:SolderJumper_2_Bridged", "IDD", SJ2, {"1": "3V3", "2": "VDD"}, at=(124.46, 147.32), in_bom=False),
        Part("JP3", "Jumper:SolderJumper_2_Bridged", "SDA pull-up", SJ2, {"1": "3V3", "2": "PU_SDA"}, at=(40.64, 134.62), in_bom=False),
        Part("R1", "Device:R", "4.7k", R0603, {"1": "PU_SDA", "2": "SDI"}, lcsc="C23162", at=(55.88, 134.62)),
        Part("JP4", "Jumper:SolderJumper_2_Bridged", "SCL pull-up", SJ2, {"1": "3V3", "2": "PU_SCL"}, at=(40.64, 147.32), in_bom=False),
        Part("R2", "Device:R", "4.7k", R0603, {"1": "PU_SCL", "2": "SCK"}, lcsc="C23162", at=(55.88, 147.32)),
        Part("R3", "Device:R", "1k", R0603, {"1": "3V3", "2": "PROM"}, lcsc="C21190", at=(71.12, 147.32)),
        Part("R4", "Device:R", "10k", R0603, {"1": "3V3", "2": "CS"}, lcsc="C25804", at=(83.82, 147.32)),
        Part("C1", "Device:C", "100nF", C0603, {"1": "VDD", "2": "GND"}, lcsc="C14663", at=(96.52, 134.62)),
        Part("C2", "Device:C", "10uF", C0603, {"1": "VDD", "2": "GND"}, lcsc="C19702", at=(106.68, 134.62)),
        Part("C3", "Device:C", "100nF", C0603, {"1": "3V3", "2": "GND"}, lcsc="C14663", at=(96.52, 147.32)),
        Part("C4", "Device:C", "10uF", C0603, {"1": "3V3", "2": "GND"}, lcsc="C19702", at=(106.68, 147.32)),
    ]


NOTES = [
    ("Board B: XIAO ESP32-S3 carrier for a Bosch Shuttle Board 3.0. Shuttle on top, XIAO underneath. 3.3 V only.\n"
     "BME690 8x shuttle: D0-D7 (GPIO1, 2, 3, 4, 5, 6, 43, 44) are the chip selects of sensors U1-U8;\n"
     "D8 SCK (GPIO7), D9 SDO/MISO (GPIO8), D10 SDI/MOSI (GPIO9). The XIAO Sense's microSD card shares\n"
     "D8-D10 (its own CS is GPIO21), so on the 8x board the card and the sensors take turns on one SPI bus.", 25.4, 22.86),
    ("Selector jumpers, set for the 8x shuttle as made (pads 1-2 joined):\n"
     "JP2: D0 -> shuttle GPIO0 (8x: sensor U1 CS). Cut 1-2, bridge 2-3: D0 -> shuttle CS (single-sensor shuttles).\n"
     "JP5: D7 -> shuttle GPIO7 (8x: sensor U8 CS). Cut 1-2, bridge 2-3: D7 -> PROM_RW (shuttle ID chip).\n"
     "JP1 IDD: cut and put a meter across J3 to measure the sensor VDD current.\n"
     "JP3 / JP4: 4.7k I2C pull-ups on SDA / SCL; cut to remove.", 25.4, 160.02),
    ("R3 1k: PROM_RW pull-up for the DS28E05 1-Wire ID chip (datasheet: 300-1500 ohm at 3.3 V,\n"
     "overdrive speed only). R4 10k: CS pull-up so single-sensor shuttles start in I2C mode.\n"
     "VDDIO is tied to the XIAO's 3V3 (its logic level), so there is no TIE jumper on this board.", 25.4, 182.88),
]


def flags():
    return [("VDD", 205.74, 50.8), ("GND", 220.98, 50.8)]


def build_sch():
    write_lib_tables(HERE)
    write_project(HERE / (NAME + ".kicad_pro"), NAME, RULES, CLASSES, PATTERNS)
    write_schematic(HERE / (NAME + ".kicad_sch"), NAME, parts(),
                    "Board B - XIAO ESP32-S3 shuttle carrier", notes=NOTES, flags=flags(),
                    comments=["Seeed XIAO ESP32-S3 / Sense carrier for a Bosch Shuttle Board 3.0",
                              "github.com/leakydata/bme690-toolkit"])


# Same JLCPCB rules as Board A (see board_a/build.py).
RULES = {
    "min_clearance": 0.15,
    "min_track_width": 0.15,
    "min_connection": 0.15,
    "min_via_diameter": 0.5,
    "min_via_annular_width": 0.13,
    "min_through_hole_diameter": 0.3,
    "min_hole_to_hole": 0.5,
    "min_hole_clearance": 0.25,
    "min_copper_edge_clearance": 0.3,
    "min_silk_clearance": 0.0,
    "min_text_height": 1.0,
    "min_text_thickness": 0.15,
    "solder_mask_to_copper_clearance": 0.0,
    "min_microvia_diameter": 0.2,
    "min_microvia_drill": 0.1,
    "min_resolved_spokes": 1,
    "allow_blind_buried_vias": False,
    "allow_microvias": False,
}
CLASSES = [netclass("Default", 0.15, 0.2), netclass("Power", 0.15, 0.4)]
PATTERNS = [("/VDD", "Power"), ("/3V3", "Power"), ("/GND", "Power")]


if __name__ == "__main__":
    step = sys.argv[1] if len(sys.argv) > 1 else "sch"
    if step == "sch":
        build_sch()
        print("schematic written")
    elif step == "pcb":
        from pcb import build_pcb
        build_pcb()

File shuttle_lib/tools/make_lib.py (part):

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HOLE = 0.60
PAD = 1.05

P1_NAMES = ["VDD", "VDDIO", "GND", "GPIO0", "GPIO1", "GPIO2/INT1", "GPIO3/INT2"]
P2_NAMES = ["CS", "SCK/SCL", "SDO", "SDI/SDA", "GPIO4", "GPIO5", "GPIO6", "GPIO7", "PROM_RW"]


def f(v):
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    """Seeed XIAO ESP32-S3, numbered like Seeed's own KiCad symbol and board
    file: 1-7 = D0-D6 down the left, 8-14 = D7, D8, D9, D10, 3V3, GND, 5V up
    the right. Names give the ESP32-S3 GPIO."""
    left = ["D0/GPIO1", "D1/GPIO2", "D2/GPIO3", "D3/GPIO4", "D4/SDA/GPIO5", "D5/SCL/GPIO6", "D6/TX/GPIO43"]
    right = ["D7/RX/GPIO44", "D8/SCK/GPIO7", "D9/MISO/GPIO8", "D10/MOSI/GPIO9", "3V3", "GND", "5V"]
    right_kind = ["bidirectional"] * 4 + ["power_out", "power_in", "power_in"]
    out = []
    out.append('\t(symbol "XIAO_ESP32S3" (pin_names (offset 1.016)) (exclude_from_sim no) (in_bom yes) (on_board yes)\n')
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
